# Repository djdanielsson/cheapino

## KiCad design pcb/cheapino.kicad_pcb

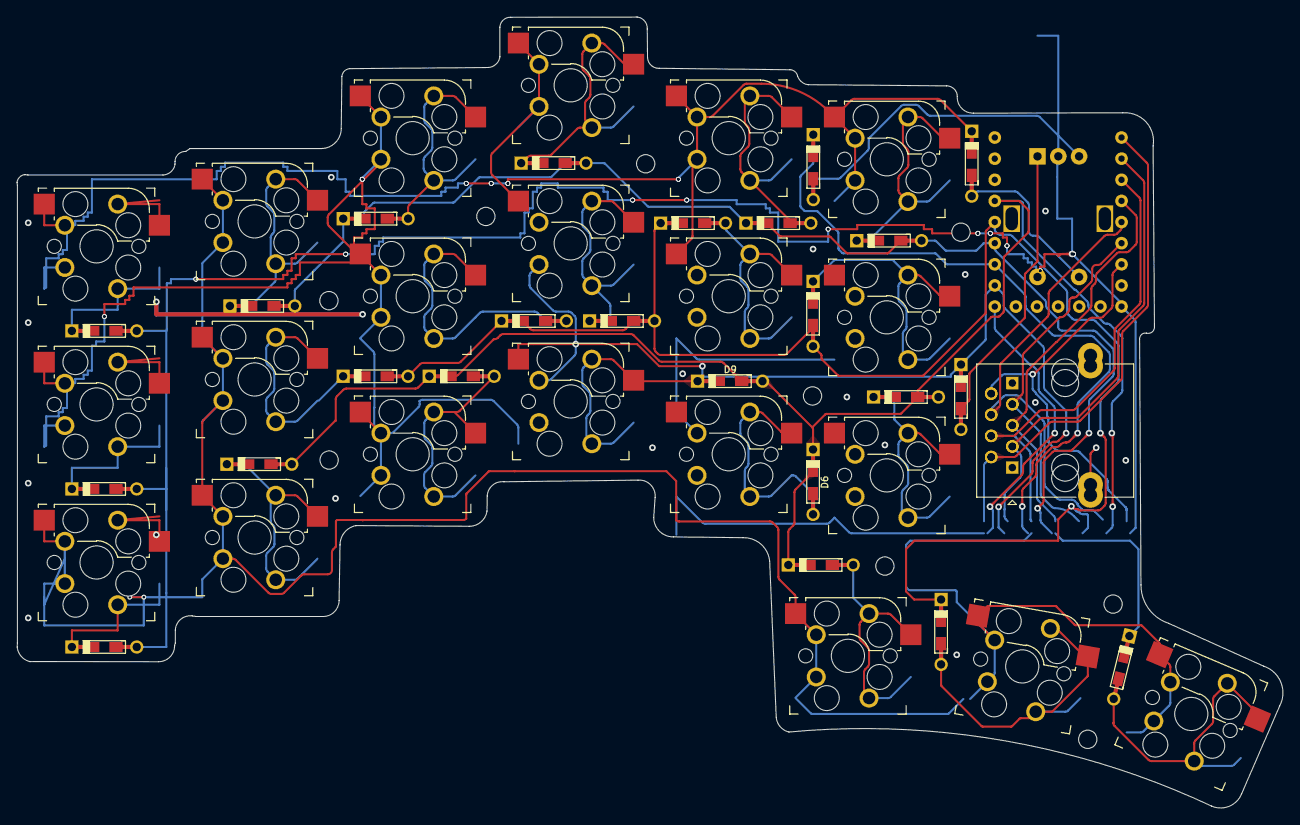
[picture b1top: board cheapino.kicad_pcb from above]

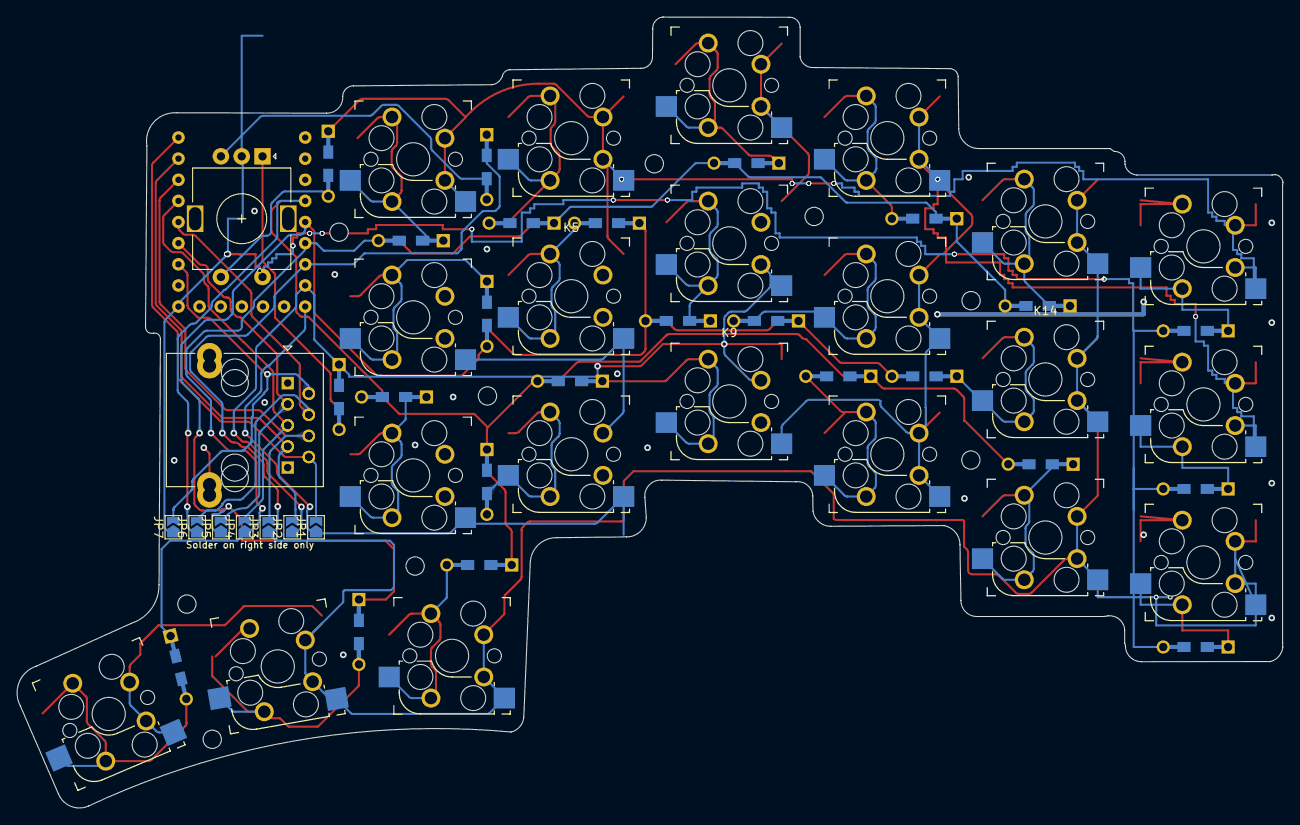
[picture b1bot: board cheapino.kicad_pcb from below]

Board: 2 copper layers, 152.2 x 95.1 mm, 56 parts (9 on the bottom side), 39 nets.

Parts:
D1, D2, D3, D4, D5, D6, D7, D8, D9, D10, D11, D12, D13, D14, D15, D16, D17, D18, D19, D20, D21: DIODE; Diode-dual
D22: D22; Diode-dual
D23: D23; Diode-dual
D24: D24; Diode-dual
ENC1: RotaryEncoder_Switch; RotaryEncoder_Alps_EC11E-Switch_Vertical_H20mm
JP1, JP2, JP3, JP4, JP5, JP6, JP7: SolderJumper_2_Open; SolderJumper-2_P1.3mm_Open_TrianglePad1.0x1.5mm
J_1_LEFT1, J_2_RIGHT1: RJ45_Shielded; RJ45_Ninigi_GE
K1, K2, K3, K4, K5, K6, K7, K8, K9, K10, K11, K12, K13, K14, K15, K16, K17, K18: SW_Push; Kailh_socket_MX_optional_reversible
K19: K19; Kailh_socket_MX_optional_reversible
K20: K20; Kailh_socket_MX_optional_reversible
K21: K21; Kailh_socket_MX_optional_reversible
U1: RP2040-Zero; MCU_RP2040_Zero_34

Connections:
COL_1: D21.1 (K), JP1.1 (A), K1.1, K2.1, K3.1, K4.1, K5.1, K6.1, K19.1, U1.14 (GP14)
COL_2: D19.1 (K), JP2.1 (A), K7.1, K8.1, K9.1, K10.1, K11.1, K12.1, K20.1, U1.15 (GP15)
COL_3: D20.1 (K), JP3.1 (A), K13.1, K14.1, K15.1, K16.1, K17.1, K18.1, K21.1, U1.26 (GP26)
GND: J_1_LEFT1.1, J_1_LEFT1.SH, J_2_RIGHT1.1, J_2_RIGHT1.SH, U1.31 (GND)
unnamed: D1.1 (K), K1.2
unnamed: D2.1 (K), K2.2
unnamed: D3.1 (K), K3.2
unnamed: D4.2 (A), K4.2
unnamed: D5.2 (A), K5.2
unnamed: D6.2 (A), K6.2
unnamed: D7.1 (K), K7.2
unnamed: D8.1 (K), K8.2
unnamed: D9.1 (K), K9.2
unnamed: D10.2 (A), K10.2
unnamed: D11.2 (A), K11.2
unnamed: D12.2 (A), K12.2
unnamed: D13.1 (K), K13.2
unnamed: D14.1 (K), K14.2
unnamed: D15.1 (K), K15.2
unnamed: D16.2 (A), K16.2
unnamed: D17.2 (A), K17.2
unnamed: D18.2 (A), K18.2
unnamed: D19.2 (A), ENC1.A
unnamed: D20.2 (A), ENC1.B
unnamed: D21.2 (A), ENC1.S1
unnamed: D22.1 (K), K19.2
unnamed: D23.1 (K), K20.2
unnamed: D24.1 (K), K21.2
ROW_1: D1.2 (A), D4.1 (K), D7.2 (A), D10.1 (K), D13.2 (A), D16.1 (K), JP4.1 (A), U1.27 (GP27)
ROW_2: D2.2 (A), D5.1 (K), D8.2 (A), D11.1 (K), D14.2 (A), D17.1 (K), JP5.1 (A), U1.28 (GP28)
ROW_3: D3.2 (A), D6.1 (K), D9.2 (A), D12.1 (K), D15.2 (A), D18.1 (K), JP6.1 (A), U1.29 (GP29)
ROW_4: D22.2 (A), D23.2 (A), D24.2 (A), ENC1.C, ENC1.S2, JP7.1 (A), U1.8 (GP8)
R_COL_1: JP1.2 (B), J_1_LEFT1.2, J_2_RIGHT1.8, U1.0 (GP0)
R_COL_2: JP2.2 (B), J_1_LEFT1.3, J_2_RIGHT1.7, U1.1 (GP1)
R_COL_3: JP3.2 (B), J_1_LEFT1.4, J_2_RIGHT1.6, U1.2 (GP2)
R_ROW_1: JP4.2 (B), J_1_LEFT1.5, J_2_RIGHT1.5, U1.3 (GP3)
R_ROW_2: JP6.2 (B), J_1_LEFT1.6, J_2_RIGHT1.4, U1.4 (GP4)
R_ROW_3: JP5.2 (B), J_1_LEFT1.7, J_2_RIGHT1.3, U1.5 (GP5)
R_ROW_4: JP7.2 (B), J_1_LEFT1.8, J_2_RIGHT1.2, U1.6 (GP6)

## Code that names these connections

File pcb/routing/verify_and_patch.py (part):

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    {"id": "load", "label": "Board file is valid KiCad S-expression", "ok": True},
    {"id": "outline", "label": "Edge.Cuts is a single closed outline", "ok": outline_ok},
    {"id": "cutout", "label": "No traces through the bottom cutout", "ok": off == 0},
    {"id": "shorts", "label": "No shorts between ROW_4 / COL_1 / COL_2 / COL_3", "ok": short_n == 0},
    {"id": "npth", "label": "New-column traces clear MX NPTH holes", "ok": npth_new == 0},
    {"id": "k19", "label": "K19 → D22 → COL_1 / ROW_4", "ok": bool(k19ok and d22ok)},
    {"id": "k20", "label": "K20 → D23 → COL_2 / ROW_4", "ok": bool(k20ok and d23ok)},
    {"id": "k21", "label": "K21 → D24 → COL_3 / ROW_4", "ok": bool(k21ok and d24ok)},
    {"id": "row4", "label": "ROW_4 reaches the RP2040 (U1 pad 8)", "ok": bool(row4ok)},
    {"id": "zones", "label": "GND pour needs Fill All Zones in KiCad before fab", "ok": False, "warn": True},
]

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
